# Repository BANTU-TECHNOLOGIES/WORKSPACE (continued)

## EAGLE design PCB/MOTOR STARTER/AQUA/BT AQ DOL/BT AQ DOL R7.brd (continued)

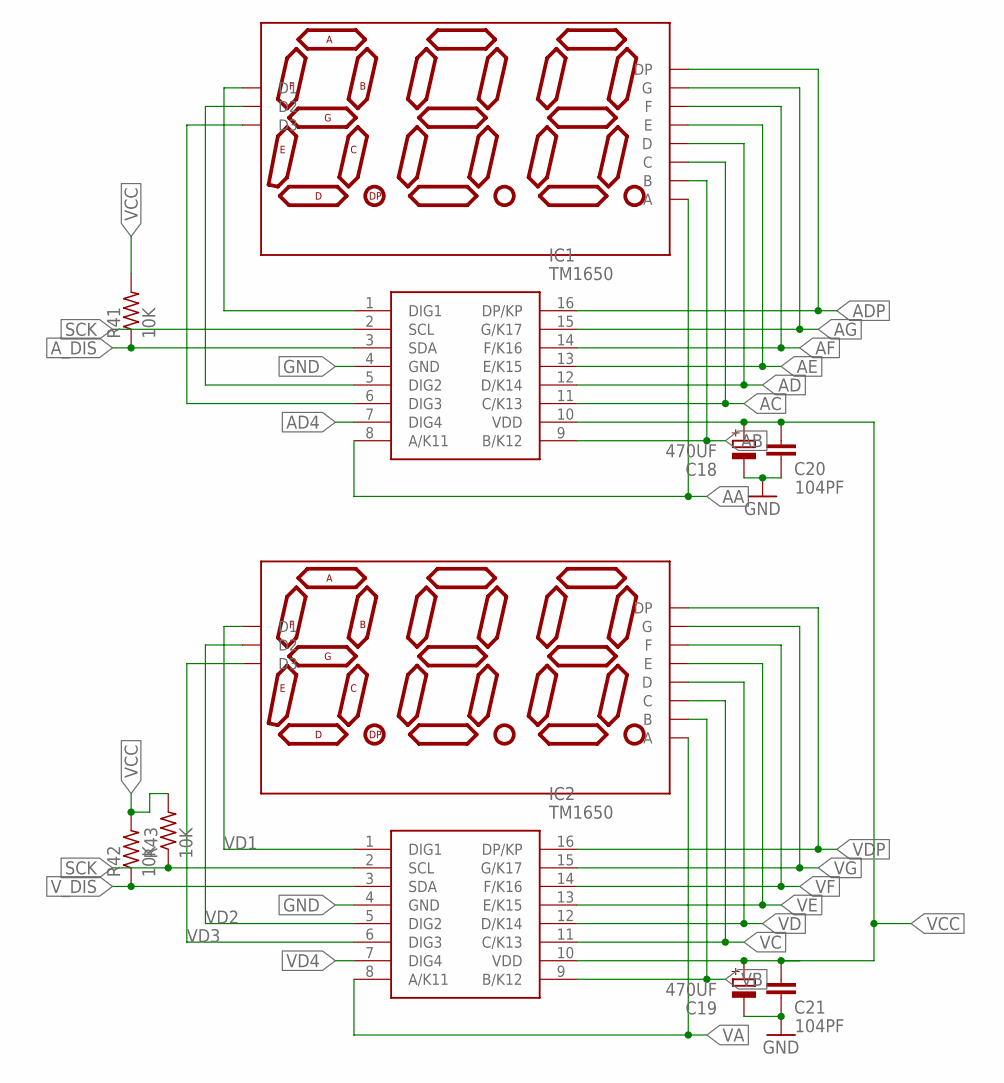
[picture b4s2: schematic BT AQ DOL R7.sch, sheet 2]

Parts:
C18, C19: 470UF; E3,5-8
C20, C21: 104PF; C1206
D17, D18: SUNR036CC3D; 7S3D036_DIP
IC1, IC2: TM1650; SOIC127P604X185-16N
R41, R42, R43: 10K; M1206

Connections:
AA: D17.11 (A), IC1.8 (A/K11); also elsewhere on the board
AB: D17.7 (B), IC1.9 (B/K12); also elsewhere on the board
AC: D17.4 (C), IC1.11 (C/K13)
AD: D17.2 (D), IC1.12 (D/K14)
AD4: IC1.7 (DIG4); also elsewhere on the board
ADP: D17.3 (DP), IC1.16 (DP/KP)
AE: D17.1 (E), IC1.13 (E/K15)
AF: D17.10 (F), IC1.14 (F/K16); also elsewhere on the board
AG: D17.5 (G), IC1.15 (G/K17)
A_DIS: IC1.3 (SDA), R41.1; also elsewhere on the board
GND: C18.-, C19.-, C20.1, C21.1, IC1.4 (GND), IC2.4 (GND); also elsewhere on the board
unnamed: D17.12 (D1), IC1.1 (DIG1)
unnamed: D17.9 (D2), IC1.5 (DIG2)
unnamed: D17.8 (D3), IC1.6 (DIG3)
SCK: IC1.2 (SCL), IC2.2 (SCL), R43.1; also elsewhere on the board
VA: D18.11 (A), IC2.8 (A/K11); also elsewhere on the board
VB: D18.7 (B), IC2.9 (B/K12)
VC: D18.4 (C), IC2.11 (C/K13); also elsewhere on the board
VCC: C18.+, C19.+, C20.2, C21.2, IC1.10 (VDD), IC2.10 (VDD), R41.2, R42.2, R43.2; also elsewhere on the board
VD: D18.2 (D), IC2.12 (D/K14); also elsewhere on the board
VD1: D18.12 (D1), IC2.1 (DIG1)
VD2: D18.9 (D2), IC2.5 (DIG2)
VD3: D18.8 (D3), IC2.6 (DIG3)
VD4: IC2.7 (DIG4); also elsewhere on the board
VDP: D18.3 (DP), IC2.16 (DP/KP)
VE: D18.1 (E), IC2.13 (E/K15); also elsewhere on the board
VF: D18.10 (F), IC2.14 (F/K16); also elsewhere on the board
VG: D18.5 (G), IC2.15 (G/K17); also elsewhere on the board
V_DIS: IC2.3 (SDA), R42.1; also elsewhere on the board

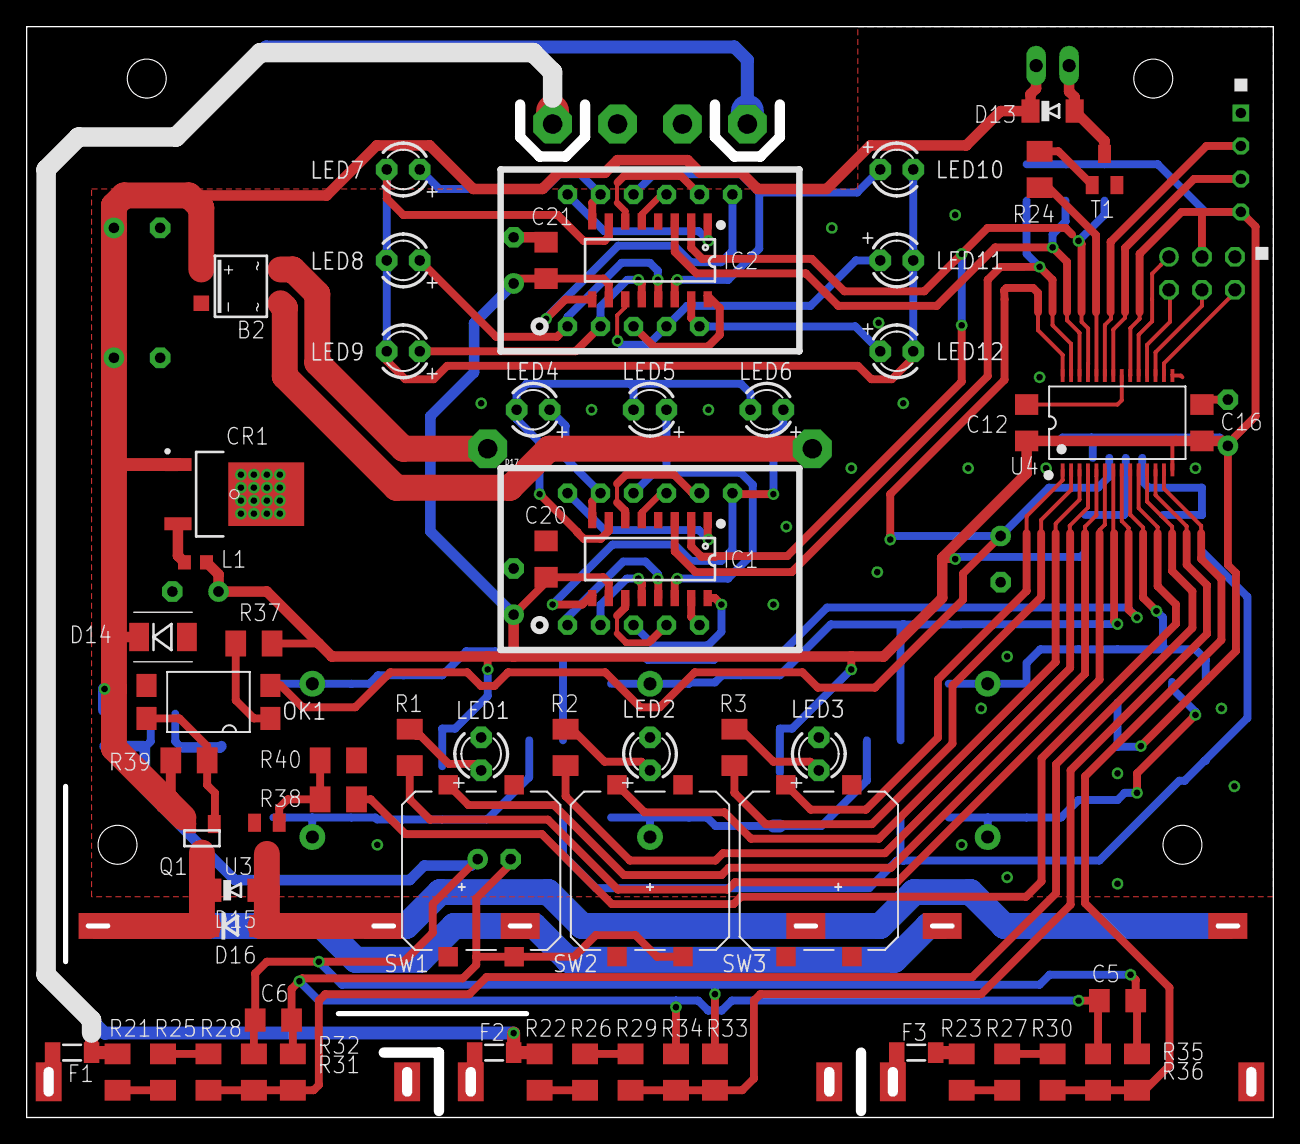
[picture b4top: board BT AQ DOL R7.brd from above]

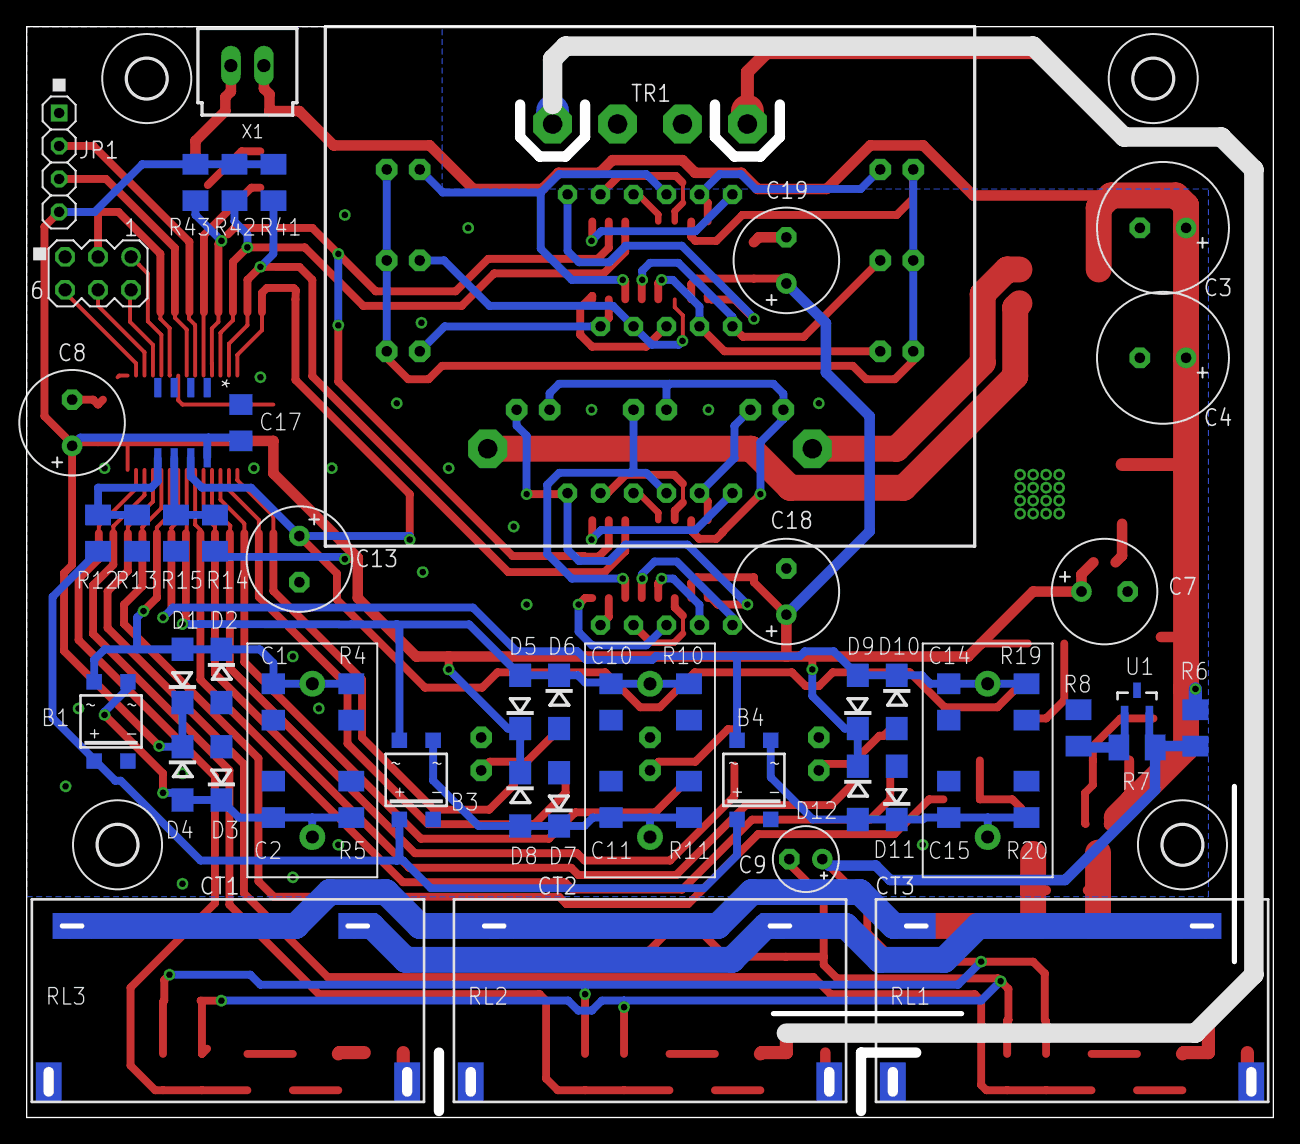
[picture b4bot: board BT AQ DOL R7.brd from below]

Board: 2 copper layers, 96.0 x 84.0 mm, 125 parts (62 on the bottom side), 84 nets.

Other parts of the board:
U$5, U$6, U$11, U$12: 3,0

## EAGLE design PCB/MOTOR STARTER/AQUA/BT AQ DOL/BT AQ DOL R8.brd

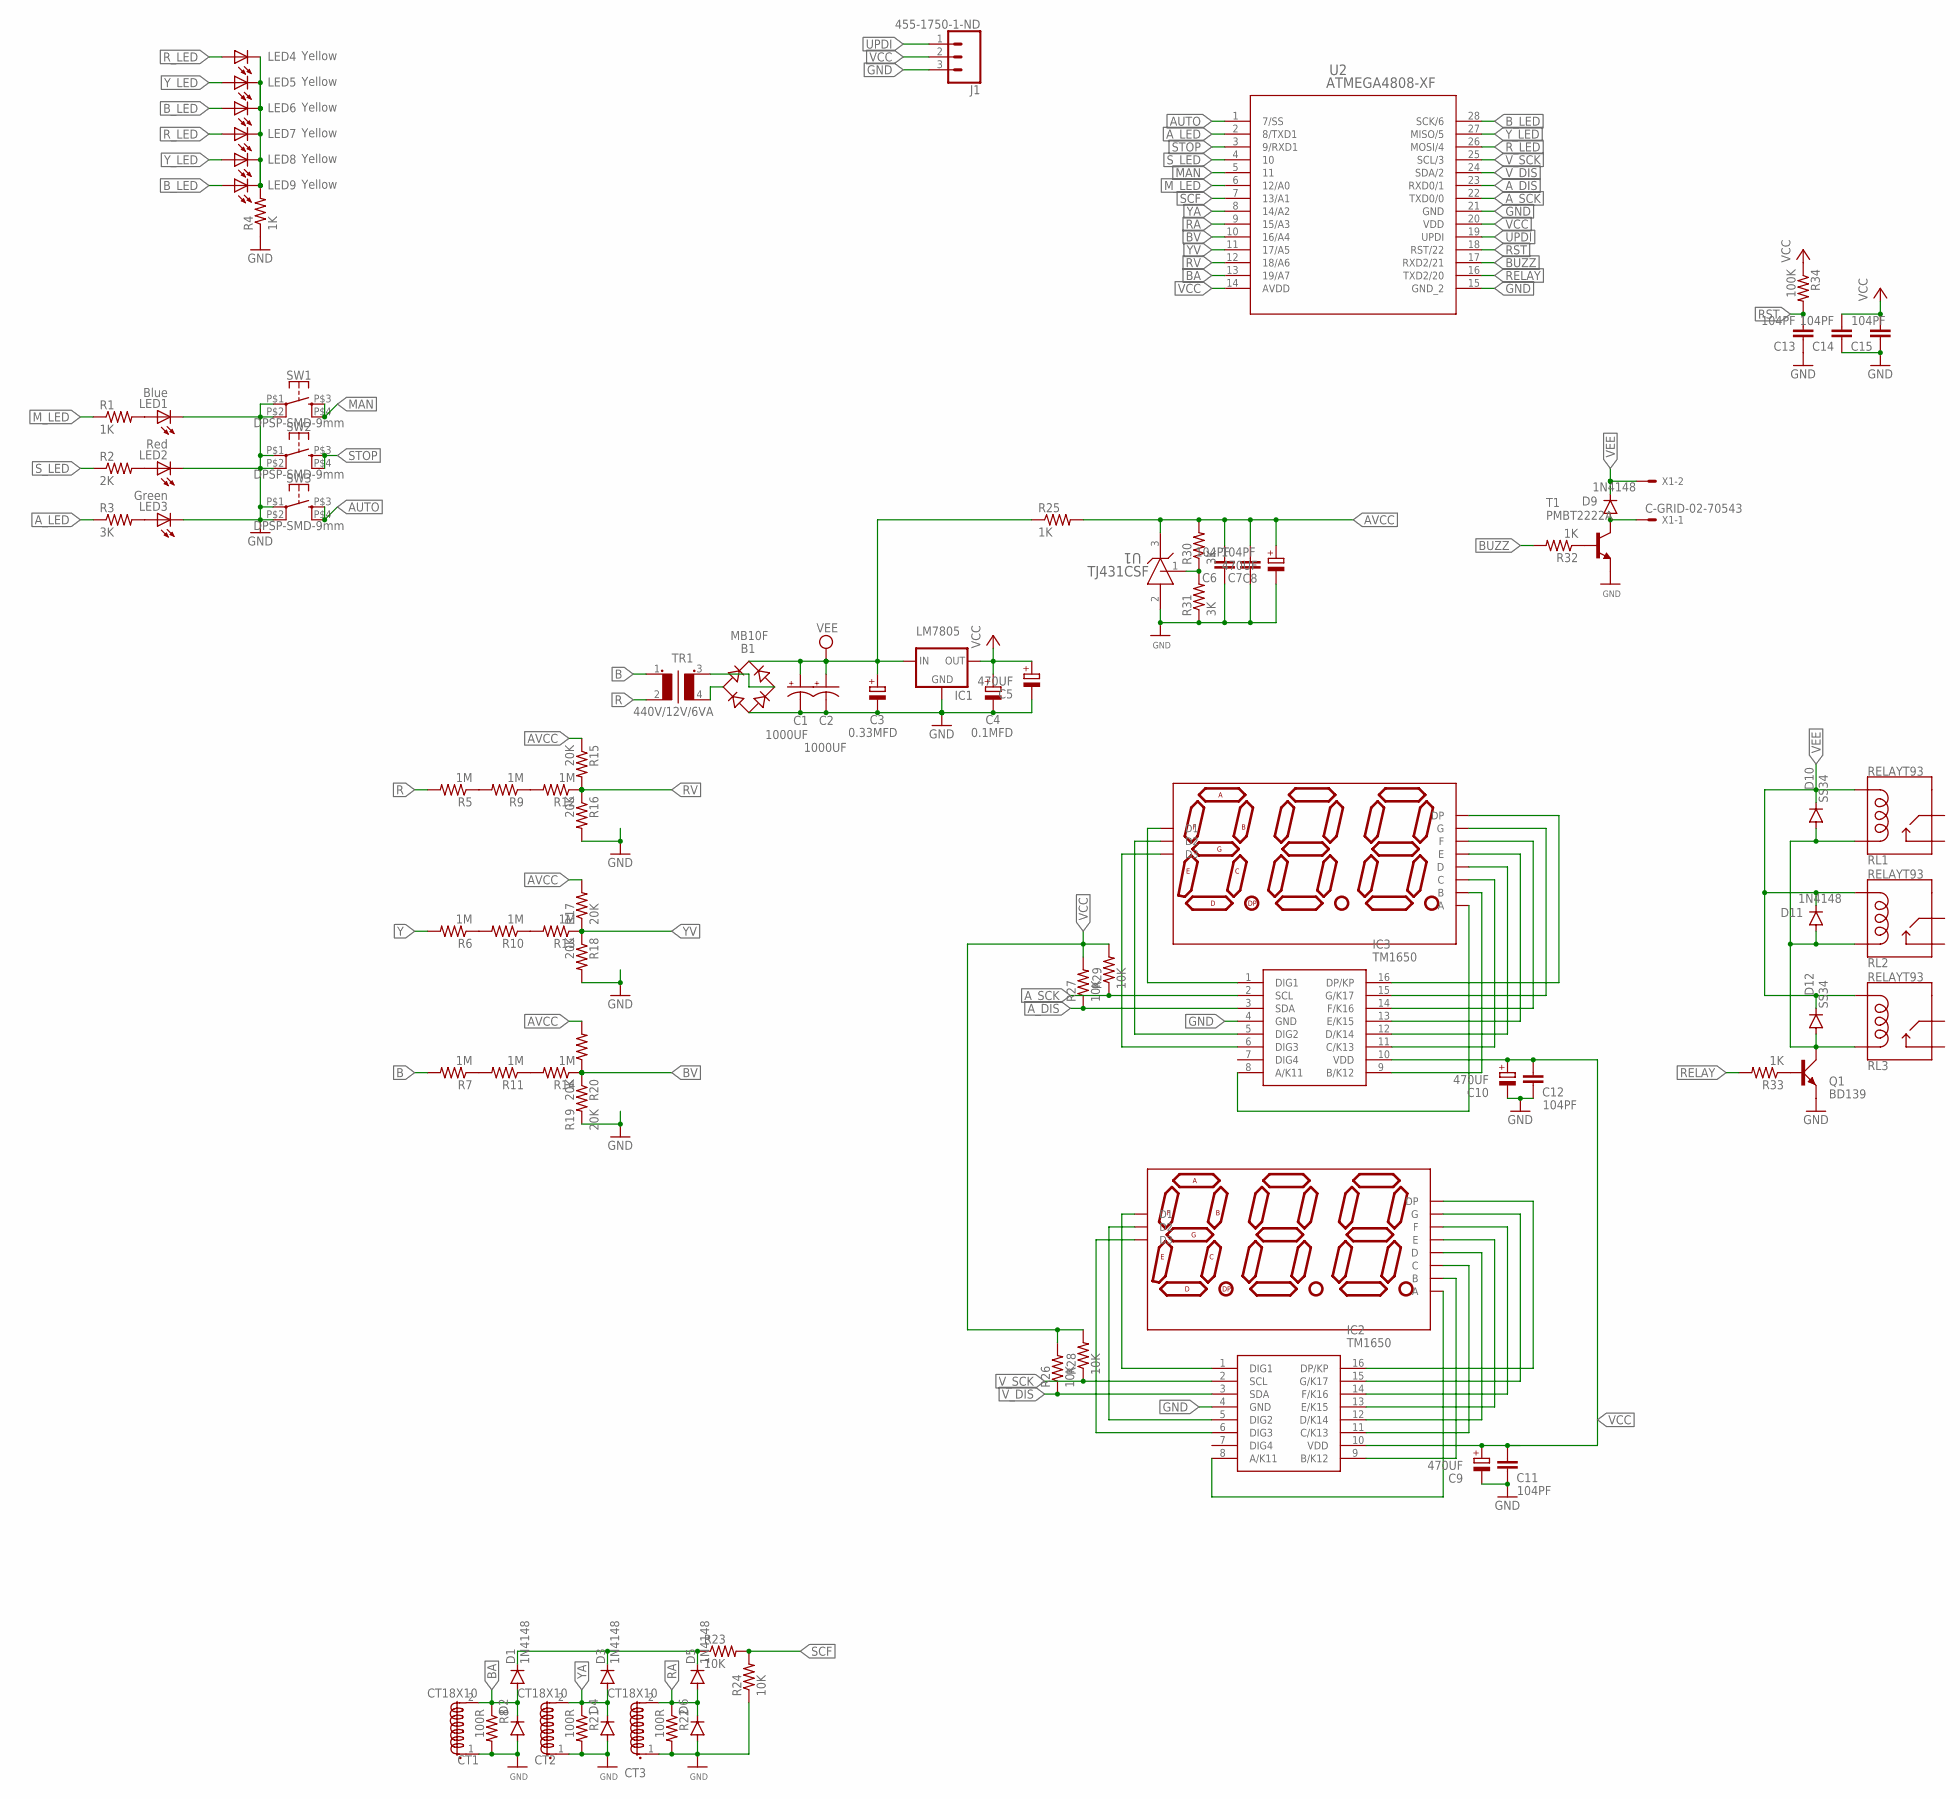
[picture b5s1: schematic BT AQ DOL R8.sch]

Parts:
B1: MB10F; SOIC-4
C1, C2: 1000UF; E3,5-10
C3: 0.33MFD; E2,5-5
C4: 0.1MFD; E2,5-5
C5, C8, C9, C10: 470UF; E3,5-8
C6, C7, C11, C12, C13, C14, C15: 104PF; C1206
CT1, CT2, CT3: CT18X10; ZMCT103C
D1, D3, D5, D9, D11: 1N4148; MINIMELF
D2, D4, D6: SMAJ12A; DO214AC
D7, D8: SUNR036CC3D; 7S3D036_DIP
D10, D12: SS34; DO-214AC
IC1: LM7805; 78XXS
IC2, IC3: TM1650; SOIC127P604X185-16N
J1: 455-1750-1-ND; 1X03
LED1: Blue; LED3MM
LED2: Red; LED3MM
LED3: Green; LED3MM
LED4, LED5, LED6, LED7, LED8, LED9: Yellow; LED3MM
Q1: BD139; TO126AV
R1, R4, R25, R32, R33: 1K; M1206
R2: 2K; M1206
R3, R30, R31: 3K; M1206
R5, R6, R7, R9, R10, R11, R12, R13, R14: 1M; M1206
R8, R21, R22: 100R; M1206
R15, R16, R17, R18, R19, R20: 20K; M1206
R23, R24, R26, R27, R28, R29: 10K; M1206
R34: 100K; M1206
RL1, RL2, RL3: RELAYT93; DT93
SW1, SW2, SW3: DPSP-SMD-9mm; B3F-40XX-ROUND-SMD
T1: PMBT2222A; SC59-BEC
TR1: 440V/12V/6VA; 440V12V6VA
U1: TJ431CSF; SOT-23
U2: ATMEGA4808-XF; SSOP28_SS_MCH
X1: C-GRID-02-70543; 70543-02

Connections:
AUTO: SW3.P$3 (3), SW3.P$4 (4), U2.1 (7/SS)
AVCC: C6.2, C7.2, C8.+, R15.1, R17.2, R19.2, R25.2, R30.2, U1.3 (CATHODE)
A_DIS: IC3.3 (SDA), R27.1, U2.23 (RXD0/1)
A_LED: R3.1, U2.2 (8/TXD1)
A_SCK: IC3.2 (SCL), R29.1, U2.22 (TXD0/0)
B: R7.2, TR1.1
BA: CT1.2 (S1.2), D1.A, D2.C, R8.1, U2.13 (19/A7)
BUZZ: R32.2, U2.17 (RXD2/21)
BV: R14.1, R19.1, R20.1, U2.10 (16/A4)
B_LED: LED6.A, LED9.A, U2.28 (SCK/6)
GND: B1.-, C1.-, C2.-, C3.-, C4.-, C5.-, C6.1, C7.1, C8.-, C9.-, C10.-, C11.1, C12.1, C13.1, C14.1, C15.1, CT1.1 (S1.1), CT2.1 (S1.1), CT3.1 (S1.1), D2.A, D4.A, D6.A, IC1.GND, IC2.4 (GND), IC3.4 (GND), J1.3, LED1.K (C), LED2.K (C), LED3.K (C), Q1.E, R4.1, R8.2, R16.2, R18.2, R20.2, R21.2, R22.2, R24.1, R31.1, SW1.P$1 (1), SW1.P$2 (2), SW2.P$1 (1), SW2.P$2 (2), SW3.P$1 (1), SW3.P$2 (2), T1.E, U1.2 (ANODE), U2.15 (GND_2), U2.21 (GND)
MAN: SW1.P$3 (3), SW1.P$4 (4), U2.5 (11)
M_LED: R1.1, U2.6 (12/A0)
unnamed: B1.~2 (AC2), TR1.3 (S1)
unnamed: B1.~1 (AC1), TR1.4 (S2)
unnamed: D9.A, T1.C, X1.1
unnamed: R32.1, T1.B
unnamed: LED1.A, R1.2
unnamed: LED2.A, R2.2
unnamed: LED3.A, R3.2
unnamed: R30.1, R31.2, U1.1 (REF)
unnamed: LED4.K (C), LED5.K (C), LED6.K (C), LED7.K (C), LED8.K (C), LED9.K (C), R4.2
unnamed: D1.C, D3.C, D5.C, R23.1
unnamed: R5.1, R9.2
unnamed: R9.1, R12.2
unnamed: R6.1, R10.2
unnamed: R7.1, R11.2
unnamed: R10.1, R13.2
unnamed: Q1.B, R33.1
unnamed: R11.1, R14.2
unnamed: D8.11 (A), IC3.8 (A/K11)
unnamed: D8.7 (B), IC3.9 (B/K12)
unnamed: D8.4 (C), IC3.11 (C/K13)
unnamed: D8.2 (D), IC3.12 (D/K14)
unnamed: D8.1 (E), IC3.13 (E/K15)
unnamed: D8.10 (F), IC3.14 (F/K16)
unnamed: D8.5 (G), IC3.15 (G/K17)
unnamed: D8.3 (DP), IC3.16 (DP/KP)
unnamed: D8.12 (D1), IC3.1 (DIG1)
unnamed: D8.9 (D2), IC3.5 (DIG2)
unnamed: D8.8 (D3), IC3.6 (DIG3)
unnamed: D7.11 (A), IC2.8 (A/K11)
unnamed: D7.7 (B), IC2.9 (B/K12)
unnamed: D7.4 (C), IC2.11 (C/K13)
unnamed: D7.2 (D), IC2.12 (D/K14)
unnamed: D7.1 (E), IC2.13 (E/K15)
unnamed: D7.10 (F), IC2.14 (F/K16)
unnamed: D7.5 (G), IC2.15 (G/K17)
unnamed: D7.3 (DP), IC2.16 (DP/KP)
unnamed: D7.12 (D1), IC2.1 (DIG1)
unnamed: D7.9 (D2), IC2.5 (DIG2)
unnamed: D7.8 (D3), IC2.6 (DIG3)
unnamed: D10.A, D11.A, D12.A, Q1.C, RL1.A1 (COIL1), RL2.A1 (COIL1), RL3.A1 (COIL1)
R: R5.2, TR1.2
RA: CT3.2 (S1.2), D5.A, D6.C, R22.1, U2.9 (15/A3)
RELAY: R33.2, U2.16 (TXD2/20)
RST: C13.2, R34.2, U2.18 (RST/22)
RV: R12.1, R15.2, R16.1, U2.12 (18/A6)
R_LED: LED4.A, LED7.A, U2.26 (MOSI/4)
SCF: R23.2, R24.2, U2.7 (13/A1)
STOP: SW2.P$3 (3), SW2.P$4 (4), U2.3 (9/RXD1)
S_LED: R2.1, U2.4 (10)
UPDI: J1.1, U2.19 (UPDI)
VCC: C4.+, C5.+, C9.+, C10.+, C11.2, C12.2, C14.2, C15.2, IC1.OUT, IC2.10 (VDD), IC3.10 (VDD), J1.2, R26.2, R27.2, R28.2, R29.2, R34.1, U2.14 (AVDD), U2.20 (VDD)
VEE: B1.+, C1.+, C2.+, C3.+, D9.C, D10.C, D11.C, D12.C, IC1.IN, R25.1, RL1.A2 (COIL2), RL2.A2 (COIL2), RL3.A2 (COIL2), X1.2
V_DIS: IC2.3 (SDA), R26.1, U2.24 (SDA/2)
V_SCK: IC2.2 (SCL), R28.1, U2.25 (SCL/3)
Y: R6.2
YA: CT2.2 (S1.2), D3.A, D4.C, R21.1, U2.8 (14/A2)
YV: R13.1, R17.1, R18.1, U2.11 (17/A5)
Y_LED: LED5.A, LED8.A, U2.27 (MISO/5)

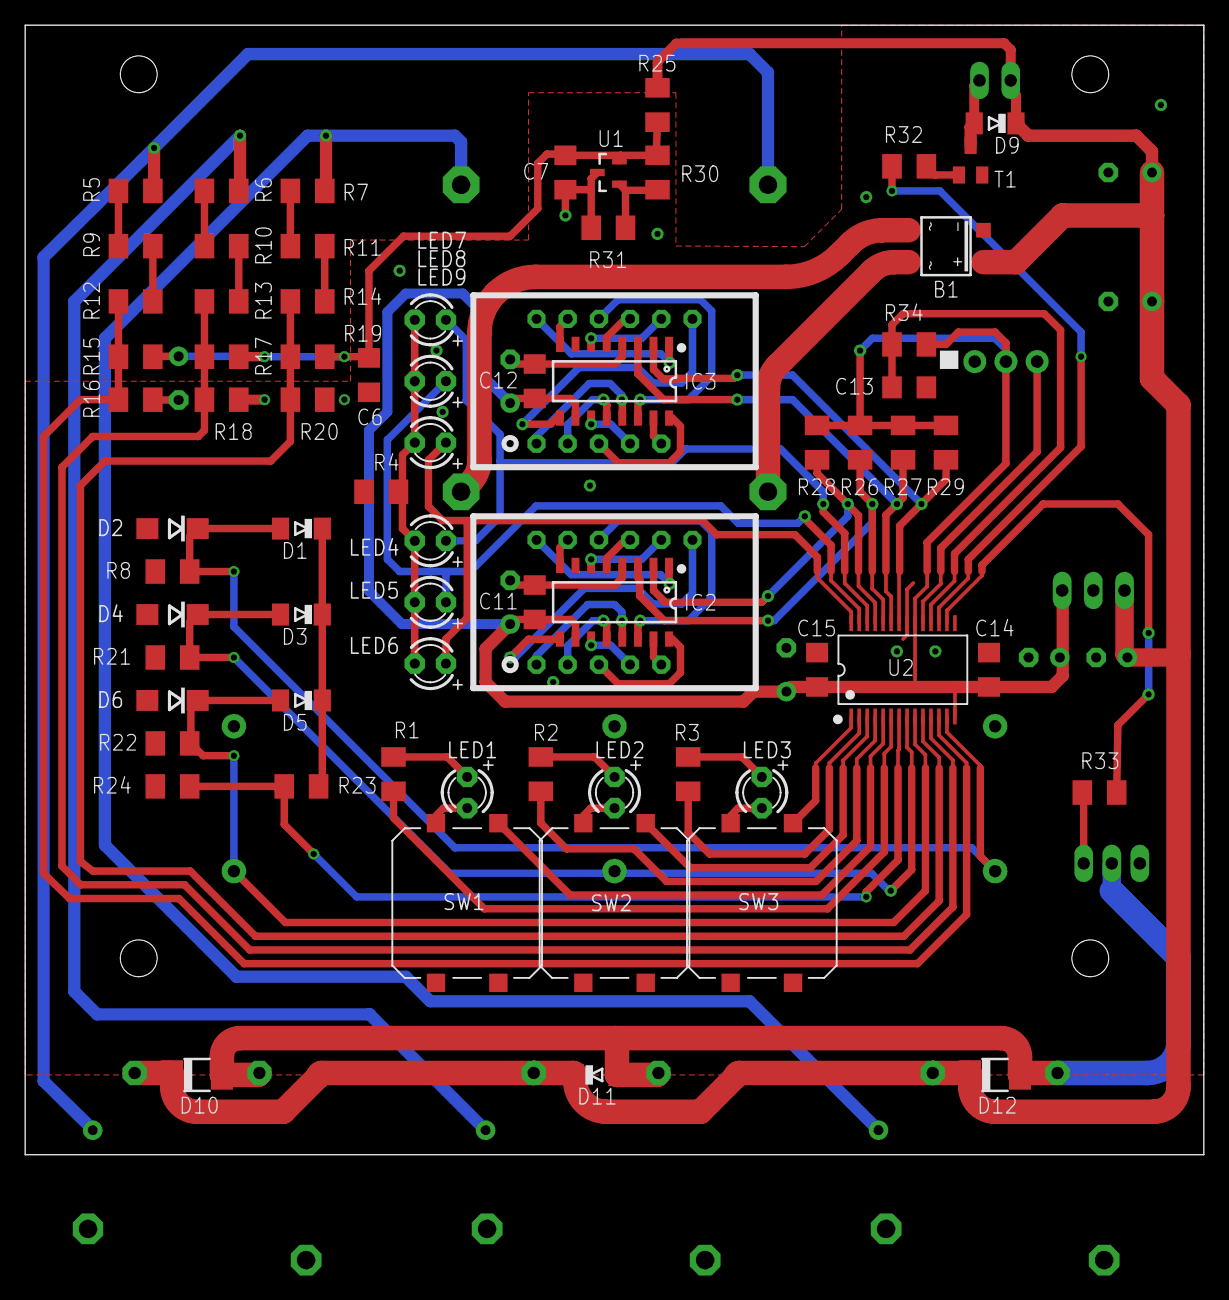
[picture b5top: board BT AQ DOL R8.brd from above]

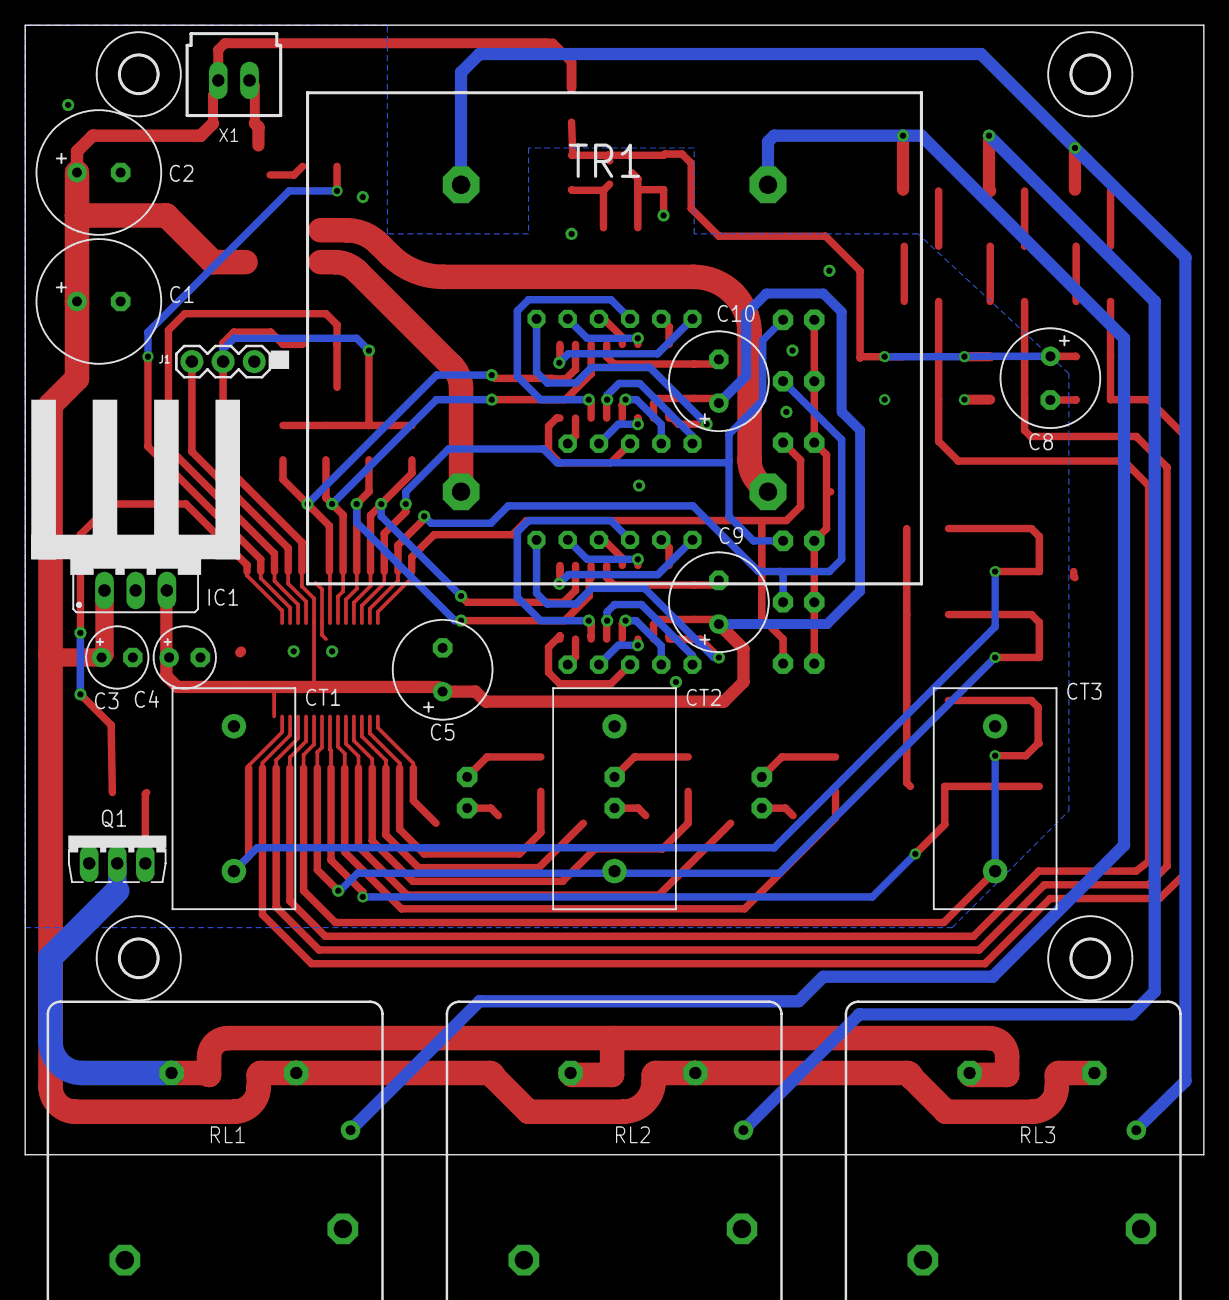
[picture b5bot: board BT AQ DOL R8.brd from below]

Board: 2 copper layers, 96.0 x 92.0 mm, 95 parts (24 on the bottom side), 70 nets.

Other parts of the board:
U$1, U$2, U$3, U$8: 3,0
U$4: TO220_17X13

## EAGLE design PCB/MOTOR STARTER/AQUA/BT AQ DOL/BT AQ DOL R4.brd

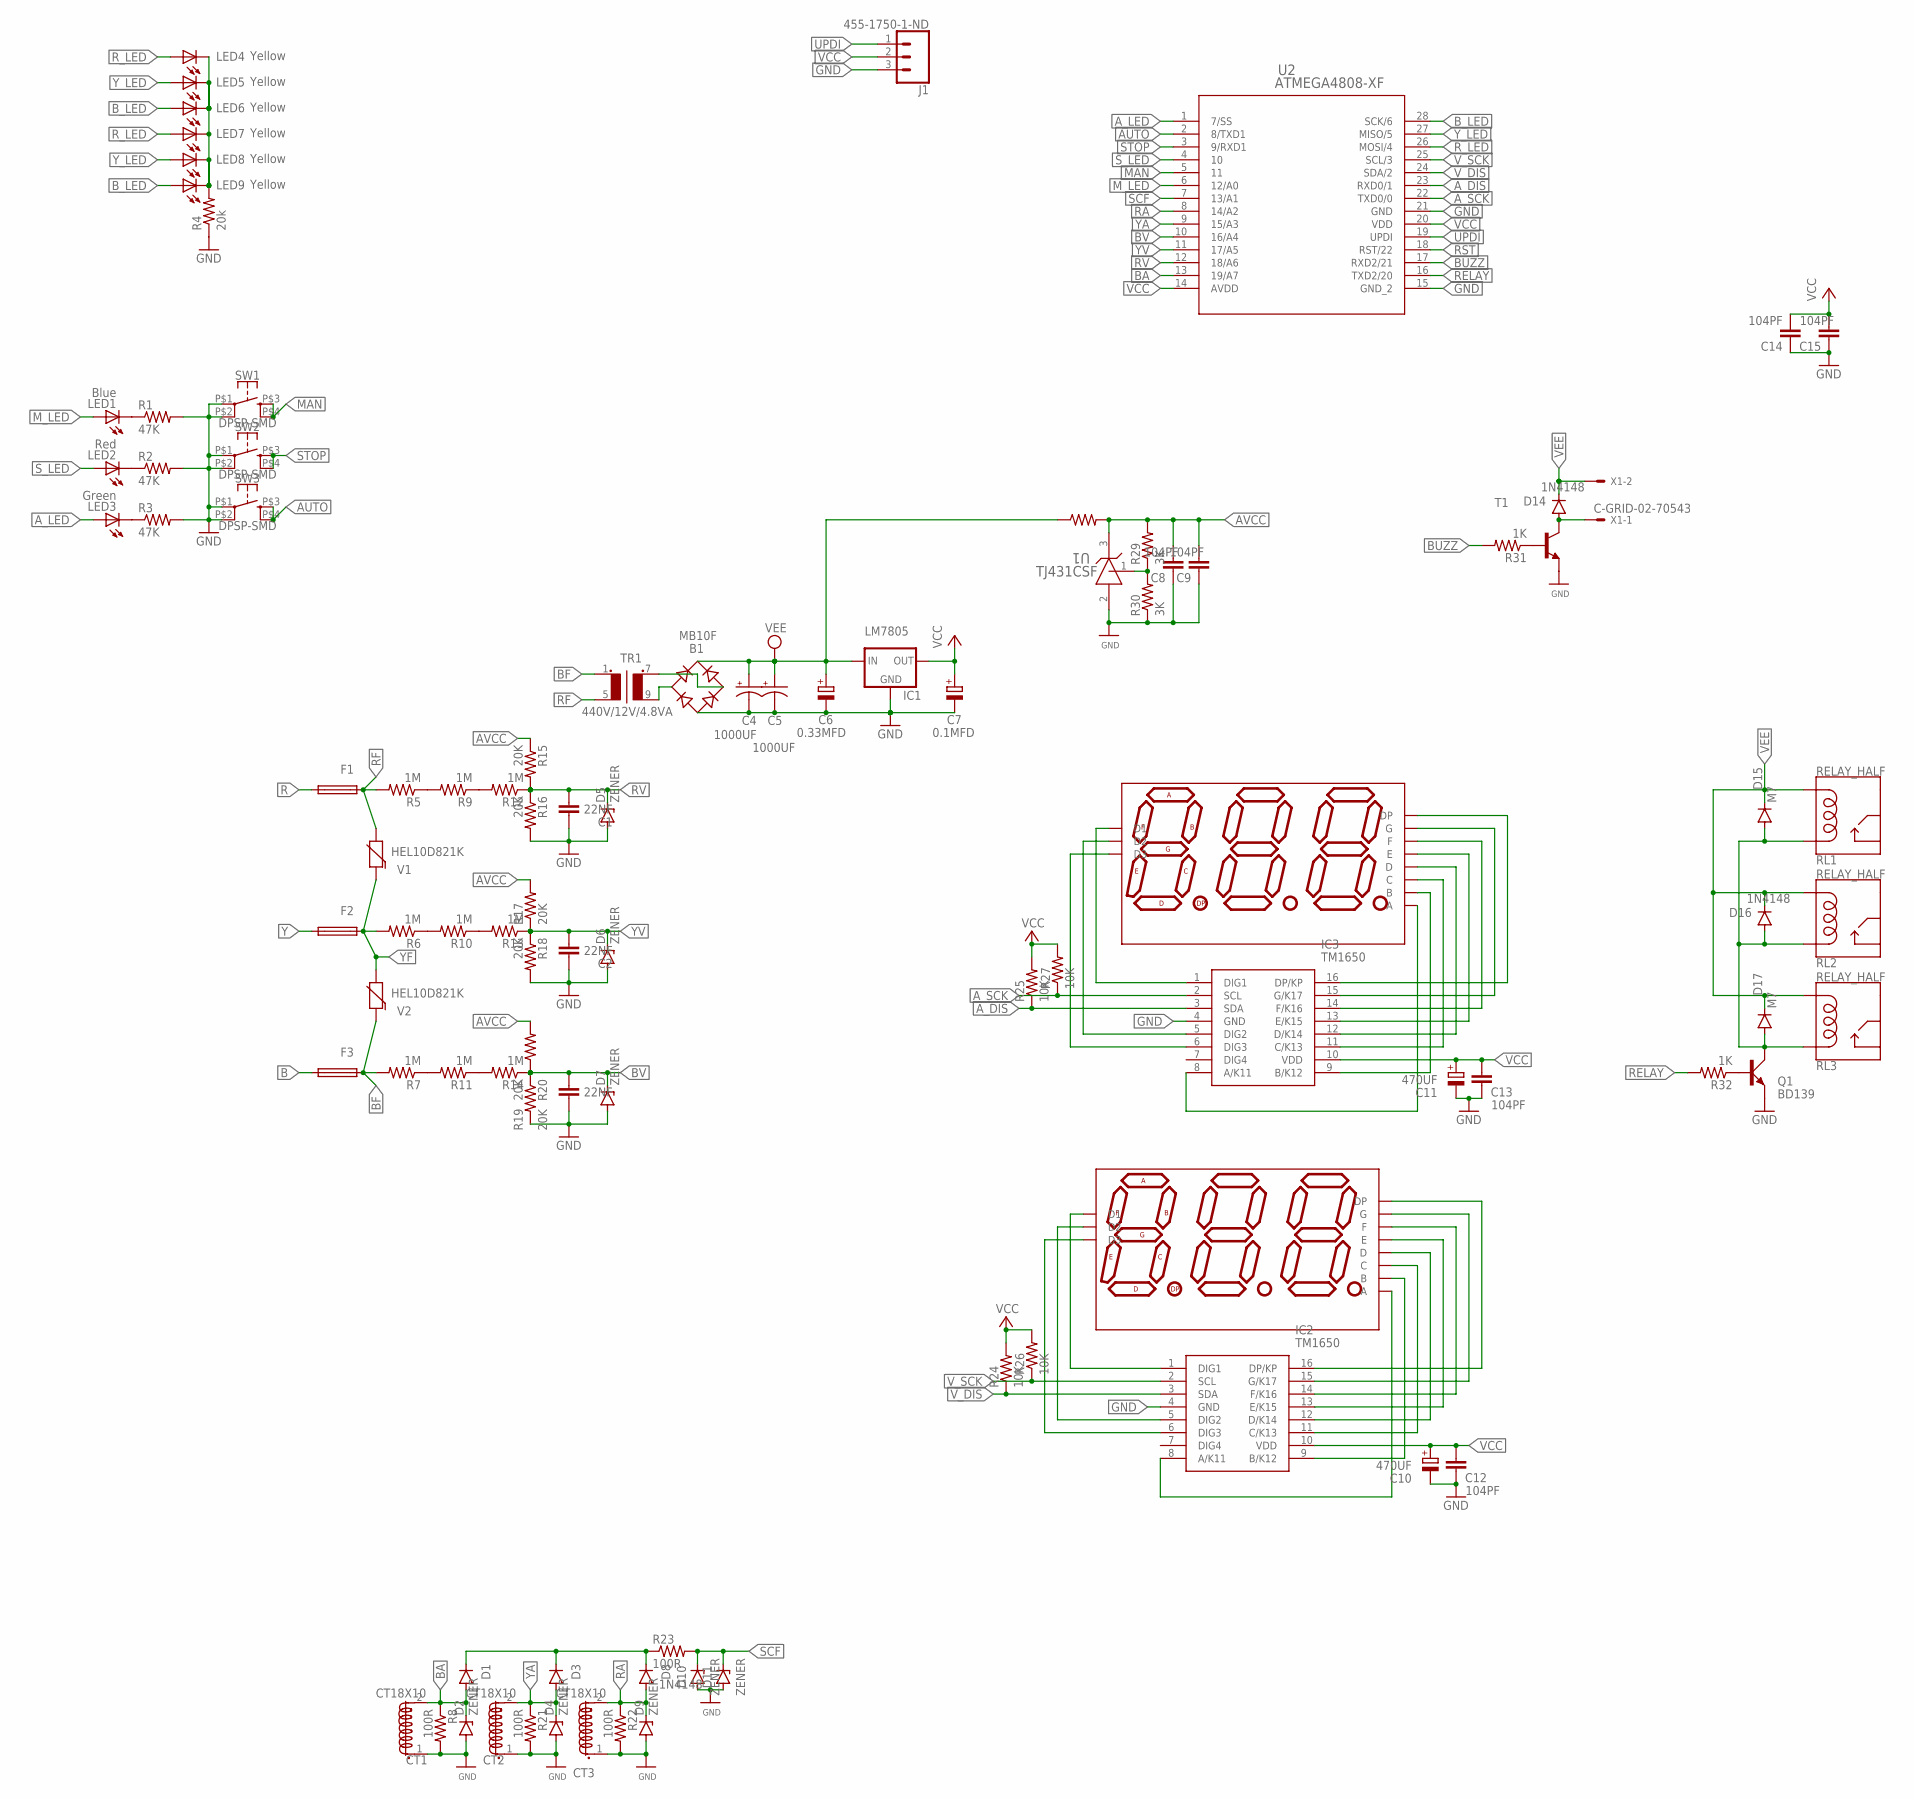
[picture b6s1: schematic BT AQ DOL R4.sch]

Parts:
B1: MB10F; SOIC-4
C1, C2, C3: 22NF; C1206
C4, C5: 1000UF; E3,5-10
C6: 0.33MFD; E2,5-5
C7: 0.1MFD; E2,5-5
C8, C9, C12, C13, C14, C15: 104PF; C1206
C10, C11: 470UF; E3,5-8
CT1, CT2, CT3: CT18X10; ZMCT103C
D1, D3, D8, D14, D16: 1N4148; MINIMELF
D2, D4, D5, D6, D7, D9, D10: ZENER; SOD6126X350
D11: ZENER; DIOMELF3516
D12, D13: SUNR036CC3D; 7S3D036_DIP
D15, D17: M7; DO-214AC
F1, F2, F3: TRF600-150
IC1: LM7805; 78XXS
IC2, IC3: TM1650; SOIC127P604X185-16N
J1: 455-1750-1-ND; 1X03
LED1: Blue; LED3MM
LED2: Red; LED3MM
LED3: Green; LED3MM
LED4, LED5, LED6, LED7, LED8, LED9: Yellow; LED3MM
Q1: BD139; TO126AV
R1, R2, R3: 47K; M1206
R4: 20k; M1206
R5, R6, R7, R9, R10, R11, R12, R13, R14: 1M; M1206
R8, R21, R22, R23: 100R; M1206
R15, R16, R17, R18, R19, R20: 20K; M1206
R24, R25, R26, R27, R28: 10K; M1206
R29, R30: 3K; M1206
R31, R32: 1K; M1206
RL1, RL2, RL3: RELAY_HALF; DT90_HALF
SW1, SW2, SW3: DPSP-SMD; B3F-40XX-ROUND-SMD
T1: MMUN2213LT1-NPN-SC59-BEC; SC59-BEC
TR1: 440V/12V/4.8VA; 440V12V6VA
U1: TJ431CSF; SOT-23
U2: ATMEGA4808-XF; SSOP28_SS_MCH
V1, V2: HEL10D821K; 10MM
X1: C-GRID-02-70543; 70543-02

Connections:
AUTO: SW3.P$3 (3), SW3.P$4 (4), U2.2 (8/TXD1)
AVCC: C8.2, C9.2, R15.1, R17.2, R19.2, R28.2, R29.2, U1.3 (CATHODE)
A_DIS: IC3.3 (SDA), R25.1, U2.23 (RXD0/1)
A_LED: LED3.A, U2.1 (7/SS)
A_SCK: IC3.2 (SCL), R27.1, U2.22 (TXD0/0)
B: F3.1
BA: CT1.2 (S1.2), D1.A, D2.1 (C), R8.1, U2.13 (19/A7)
BF: F3.2, R7.2, TR1.1, V2.1
BUZZ: R31.2, U2.17 (RXD2/21)
BV: C3.2, D7.1 (C), R14.1, R19.1, R20.1, U2.10 (16/A4)
B_LED: LED6.A, LED9.A, U2.28 (SCK/6)
GND: B1.-, C1.1, C2.1, C3.1, C4.-, C5.-, C6.-, C7.-, C8.1, C9.1, C10.-, C11.-, C12.1, C13.1, C14.1, C15.1, CT1.1 (S1.1), CT2.1 (S1.1), CT3.1 (S1.1), D2.2 (A), D4.2 (A), D5.2 (A), D6.2 (A), D7.2 (A), D9.2 (A), D10.2 (A), D11.2 (A), IC1.GND, IC2.4 (GND), IC3.4 (GND), J1.3, Q1.E, R1.2, R2.2, R3.2, R4.1, R8.2, R16.2, R18.2, R20.2, R21.2, R22.2, R30.1, SW1.P$1 (1), SW1.P$2 (2), SW2.P$1 (1), SW2.P$2 (2), SW3.P$1 (1), SW3.P$2 (2), T1.E, U1.2 (ANODE), U2.15 (GND_2), U2.21 (GND)
MAN: SW1.P$3 (3), SW1.P$4 (4), U2.5 (11)
M_LED: LED1.A, U2.6 (12/A0)
unnamed: B1.~2 (AC2), TR1.7 (S1)
unnamed: B1.~1 (AC1), TR1.9 (S2)
unnamed: D14.A, T1.C, X1.1
unnamed: R31.1, T1.B
unnamed: LED3.K (C), R3.1
unnamed: LED2.K (C), R2.1
unnamed: LED1.K (C), R1.1
unnamed: R29.1, R30.2, U1.1 (REF)
unnamed: LED4.K (C), LED5.K (C), LED6.K (C), LED7.K (C), LED8.K (C), LED9.K (C), R4.2
unnamed: D1.C, D3.C, D8.C, R23.1
unnamed: R5.1, R9.2
unnamed: R9.1, R12.2
unnamed: R6.1, R10.2
unnamed: R7.1, R11.2
unnamed: R10.1, R13.2
unnamed: Q1.B, R32.1
unnamed: R11.1, R14.2
unnamed: D13.11 (A), IC3.8 (A/K11)
unnamed: D13.7 (B), IC3.9 (B/K12)
unnamed: D13.4 (C), IC3.11 (C/K13)
unnamed: D13.2 (D), IC3.12 (D/K14)
unnamed: D13.1 (E), IC3.13 (E/K15)
unnamed: D13.10 (F), IC3.14 (F/K16)
unnamed: D13.5 (G), IC3.15 (G/K17)
unnamed: D13.3 (DP), IC3.16 (DP/KP)
unnamed: D13.12 (D1), IC3.1 (DIG1)
unnamed: D13.9 (D2), IC3.5 (DIG2)
unnamed: D13.8 (D3), IC3.6 (DIG3)
unnamed: D12.11 (A), IC2.8 (A/K11)
unnamed: D12.7 (B), IC2.9 (B/K12)
unnamed: D12.4 (C), IC2.11 (C/K13)
unnamed: D12.2 (D), IC2.12 (D/K14)
unnamed: D12.1 (E), IC2.13 (E/K15)
unnamed: D12.10 (F), IC2.14 (F/K16)
unnamed: D12.5 (G), IC2.15 (G/K17)
unnamed: D12.3 (DP), IC2.16 (DP/KP)
unnamed: D12.12 (D1), IC2.1 (DIG1)
unnamed: D12.9 (D2), IC2.5 (DIG2)
unnamed: D12.8 (D3), IC2.6 (DIG3)
unnamed: D15.A, D16.A, D17.A, Q1.C, RL1.1 (COIL1), RL2.1 (COIL1), RL3.1 (COIL1)
R: F1.1
RA: CT3.2 (S1.2), D8.A, D9.1 (C), R22.1, U2.8 (14/A2)
RELAY: R32.2, U2.16 (TXD2/20)
RF: F1.2, R5.2, TR1.5 (P2), V1.2
RST: U2.18 (RST/22)
RV: C1.2, D5.1 (C), R12.1, R15.2, R16.1, U2.12 (18/A6)
R_LED: LED4.A, LED7.A, U2.26 (MOSI/4)
SCF: D10.1 (C), D11.1 (C), R23.2, U2.7 (13/A1)
STOP: SW2.P$3 (3), SW2.P$4 (4), U2.3 (9/RXD1)
S_LED: LED2.A, U2.4 (10)
UPDI: J1.1, U2.19 (UPDI)
VCC: C7.+, C10.+, C11.+, C12.2, C13.2, C14.2, C15.2, IC1.OUT, IC2.10 (VDD), IC3.10 (VDD), J1.2, R24.2, R25.2, R26.2, R27.2, U2.14 (AVDD), U2.20 (VDD)
VEE: B1.+, C4.+, C5.+, C6.+, D14.C, D15.C, D16.C, D17.C, IC1.IN, R28.1, RL1.2 (COIL2), RL2.2 (COIL2), RL3.2 (COIL2), X1.2
V_DIS: IC2.3 (SDA), R24.1, U2.24 (SDA/2)
V_SCK: IC2.2 (SCL), R26.1, U2.25 (SCL/3)
Y: F2.1
YA: CT2.2 (S1.2), D3.A, D4.1 (C), R21.1, U2.9 (15/A3)
YF: F2.2, R6.2, V1.1, V2.2
YV: C2.2, D6.1 (C), R13.1, R17.1, R18.1, U2.11 (17/A5)
Y_LED: LED5.A, LED8.A, U2.27 (MISO/5)
